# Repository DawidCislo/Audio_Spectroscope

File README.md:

# Audio_Spectroscope

This is an Audio Spectroscope made without using any kind of programmable devices. It uses over 120 ICs such as operational amplifiers, comparators and logic gates to create the effect you can see in the preview above.

# Theory of operation
The device consists of 11 PCBs, one backplane and 10 display modules. You can find the KiCad project files for the backplane in the 'ASP_Backplane' folder, and files for the display modules in the 'ASP_DIsplay' folder. On the backplane there are 2 3.5mm TRS sockets. Both of them are connected together, and the user can plug the source to one of the sockets, and headphones or speakers to the other, so there's no need to use a splitter. Next using a set of jumpers (JP1, JP2, JP3) the user can use either the left, right or both channels as the input for the spectroscope. Jumpers feed into a preamp with user-adjustable gain (U4A), so both quitet and loud listeners can see the spectroscope work. The series shottky diode (D4) protects the preamp from voltage spikes coming from the audio input and can be omitted.

The preamp feeds into 10 active band-pass filters that separate the audio signals into different bands. Those bands are: 32Hz, 63Hz, 125Hz, 250Hz, 500Hz, 1kHz, 2kHz, 4kHz, 8kHz and 16kHz. Each band is connected to a separate display module connector.

The backplane also has a power connector (5.5/2.1mm DC jack, center positive), for use with an external 12V 1A power supply, with a switch and some basic overvoltage protection. You can save on component cost by replacing the power switch (SW1) with a jumper, so that the device will always be on, and you can omit the TVS diode (D1) and replace both the fuse (F1) and reverse-circuit protection diode (D3) with a short - this will reduce resistance to voltage spikes coming from the external power supply.

Device uses an LM2576T for generating the 5V rail, the circuit has a voltage divider with resistor values calculated for an adjustable version of LM2576T, but if a fixed 5V version of this IC is available, simply omit R13 during assembly and replace R12 with a short.

Backplane also has a -10V source built using an MC34063 multi-purpose controller. Due to low current draw on the -10V rail, internal switching transistor is sufficient, simplifying the design.

Each display module has two peak detectors connected in series. The first detector made up of U3A, D1 and U3B has a smaller hold capacitor C12 and it's quickly discharged by R34. Output of this peak detector will show the current amplitude of a filtered audio signal. Next peak detector (U3C, D2 U3D) has a larger hold capacitor and it does not have a discharge resistor. Since it's connected to U3D and D2 it will still discharge, because of non-zero leakage currents of those components. Output of this slow peak detector will show the maximum amplitude of the audio signal and hold it there for a short while.

Both the fast and slow peak detector outputs are connected to 12 comparators each. Reference levels for the comparators are set by a long voltage divider in the middle. If a voltage on the input line is higher than the reference voltage set by the resistors, a comparator pulls the output low (since it has an open-collector output). In effect, the higher the voltage on the input line, the more comparators are switched off, and the more of their outputs have a logic low. On the fast side the comparators connect to logic NOT gates through some simple Resistor-Diode level shifter. On the slow side the comparators feed through voltage level shifters into Ex-OR gates. Each Ex-Or gate is connected to both it's own comparator, and the next comparator. If both of the comparator outputs are the same, the gate's output is low. Only in a situation, when the current level is different from the next one, the gate has a logic 1 on its output. As a result, for example, the fast side outputs '000001111111' while the slow side wil only output '000001000000'. 

The LEDs are driven by a pair of transistors each (Q2, Q3, Q4 ...). One transistor is controlled by the slow side, while the other one is controlled by the fast side. Transistors are connected in such a way, that either one can independently turn the LED on. Current of the LEDs is set by the series resistors (R8, R9, R10 ...), increasing the value of these resistors decreases the brightness of the LED, and reducing the value increases it. Different LEDs from different manufacturers might need adjustment of these resistor values to achieve a matching brightness for different colors. During the assembly of the first prototype I bought new red and green LEDs, but used old yellow LEDs that I had in stock. Since the old LEDs were much dimmer than the new ones, I used a lower value of resistance for yellow LEDs. Results may vary for your LEDs and it's much better to check them before soldering all 10 display modules.

#  Assembly tips and troubleshooting
>[!CAUTION]
>This device is ***VERY CHALLENGING TO ASSEMBLE*** There is a lot of small and hard to solder components (0603, TSSOP with 0.65mm pin pitch 4x0603 resistor networks, SOT-363s) packed very close together. On top of that there's over 1200 components to solder in total, and it will take very long time to assemble.
I recommend testing every PCB before connecting them together:
- Display modules: Connect all the supply rails on the angled connector to a corresponding voltage source, preferably use a multi-rail adjustable power supply. Next, connect the input of the display module to a potentiometer, generating a voltage between 0V and 5V. See if all the LEDs light up. Next rapidly turn the potentiometer down and see if all the LEDs light up as the slow peak detector discharges. If you see LEDs that are permamently off, check the series resistors and dual transistors next to the LEDs. If whole 4x or 6x sections refuse to light up or stay always on, check the ICs. If single LEDs stay on or light up in the wrong order, check the resistor networks. If the whole module refuses to light up, check the peak detector.
- Backplane: Check if there is no short on any power rails by sticking two pieces of wire into any of the display module connector and using a multimeter in a continuity mode. If there are no shorts on any of the rails, connect the external power supply, and then using the same 2 wires and a multimeter, now in voltage mode, check if all the supply rails have a correct voltage. Note: having a slightly lower voltage on both the 12V and -10V is still fine and will not prevent the device from wirking correctly.
Only after each PCB is thoroughly tested, you can connect them all together and see if the device really works. Display modules are packed very close together, so make sure that the LEDs don't short to the neighbouring modules. Now connect the audio cable and use an online tone generator ([like this one](https://www.szynalski.com/tone-generator/)) to test if the band-pass filters are working correctly.

If everything is working as it should, you can go ahead and assemble it together. I used a set of long M3 screws to tie all the display modules together and used a [TEKAL 31.29](https://www.tme.eu/pl/details/tekal31.29/obudowy-z-panelem/teko/tekal-31-29/) case. I've used thin strips of gray foil to stop light from bleeding between LEDs. In this preview you can see the first prototype, which had several major errors - they have been fixed and the files shared in this repository should be all good. On the animated preview and here, only 9 display modules are fitted - last module is broken and I can't figure out what exactly is wrong with it.
> [!NOTE]
> All those ICs packed so close together get pretty hot, and the hotter the circuit gets, the larger leakage currents are, and the faster the 'slow' peak detector falls. Drill a few ventillation holes or use a thermal pad to help dissipate the heat.

## Other information 
The project files were last edited in KiCad 7.0.9 and can be opened by any version that's newer than that.

Symbols and footprints used to create this project are part of my library, you can get it and use it for your projects here: [alternatekicadlibrary.com](https://alternatekicadlibrary.com/).

All the content within this repository is dedicated to the public domain under the [CC0 1.0 Universal (CC0 1.0) Public Domain Dedication](https://creativecommons.org/publicdomain/zero/1.0/).

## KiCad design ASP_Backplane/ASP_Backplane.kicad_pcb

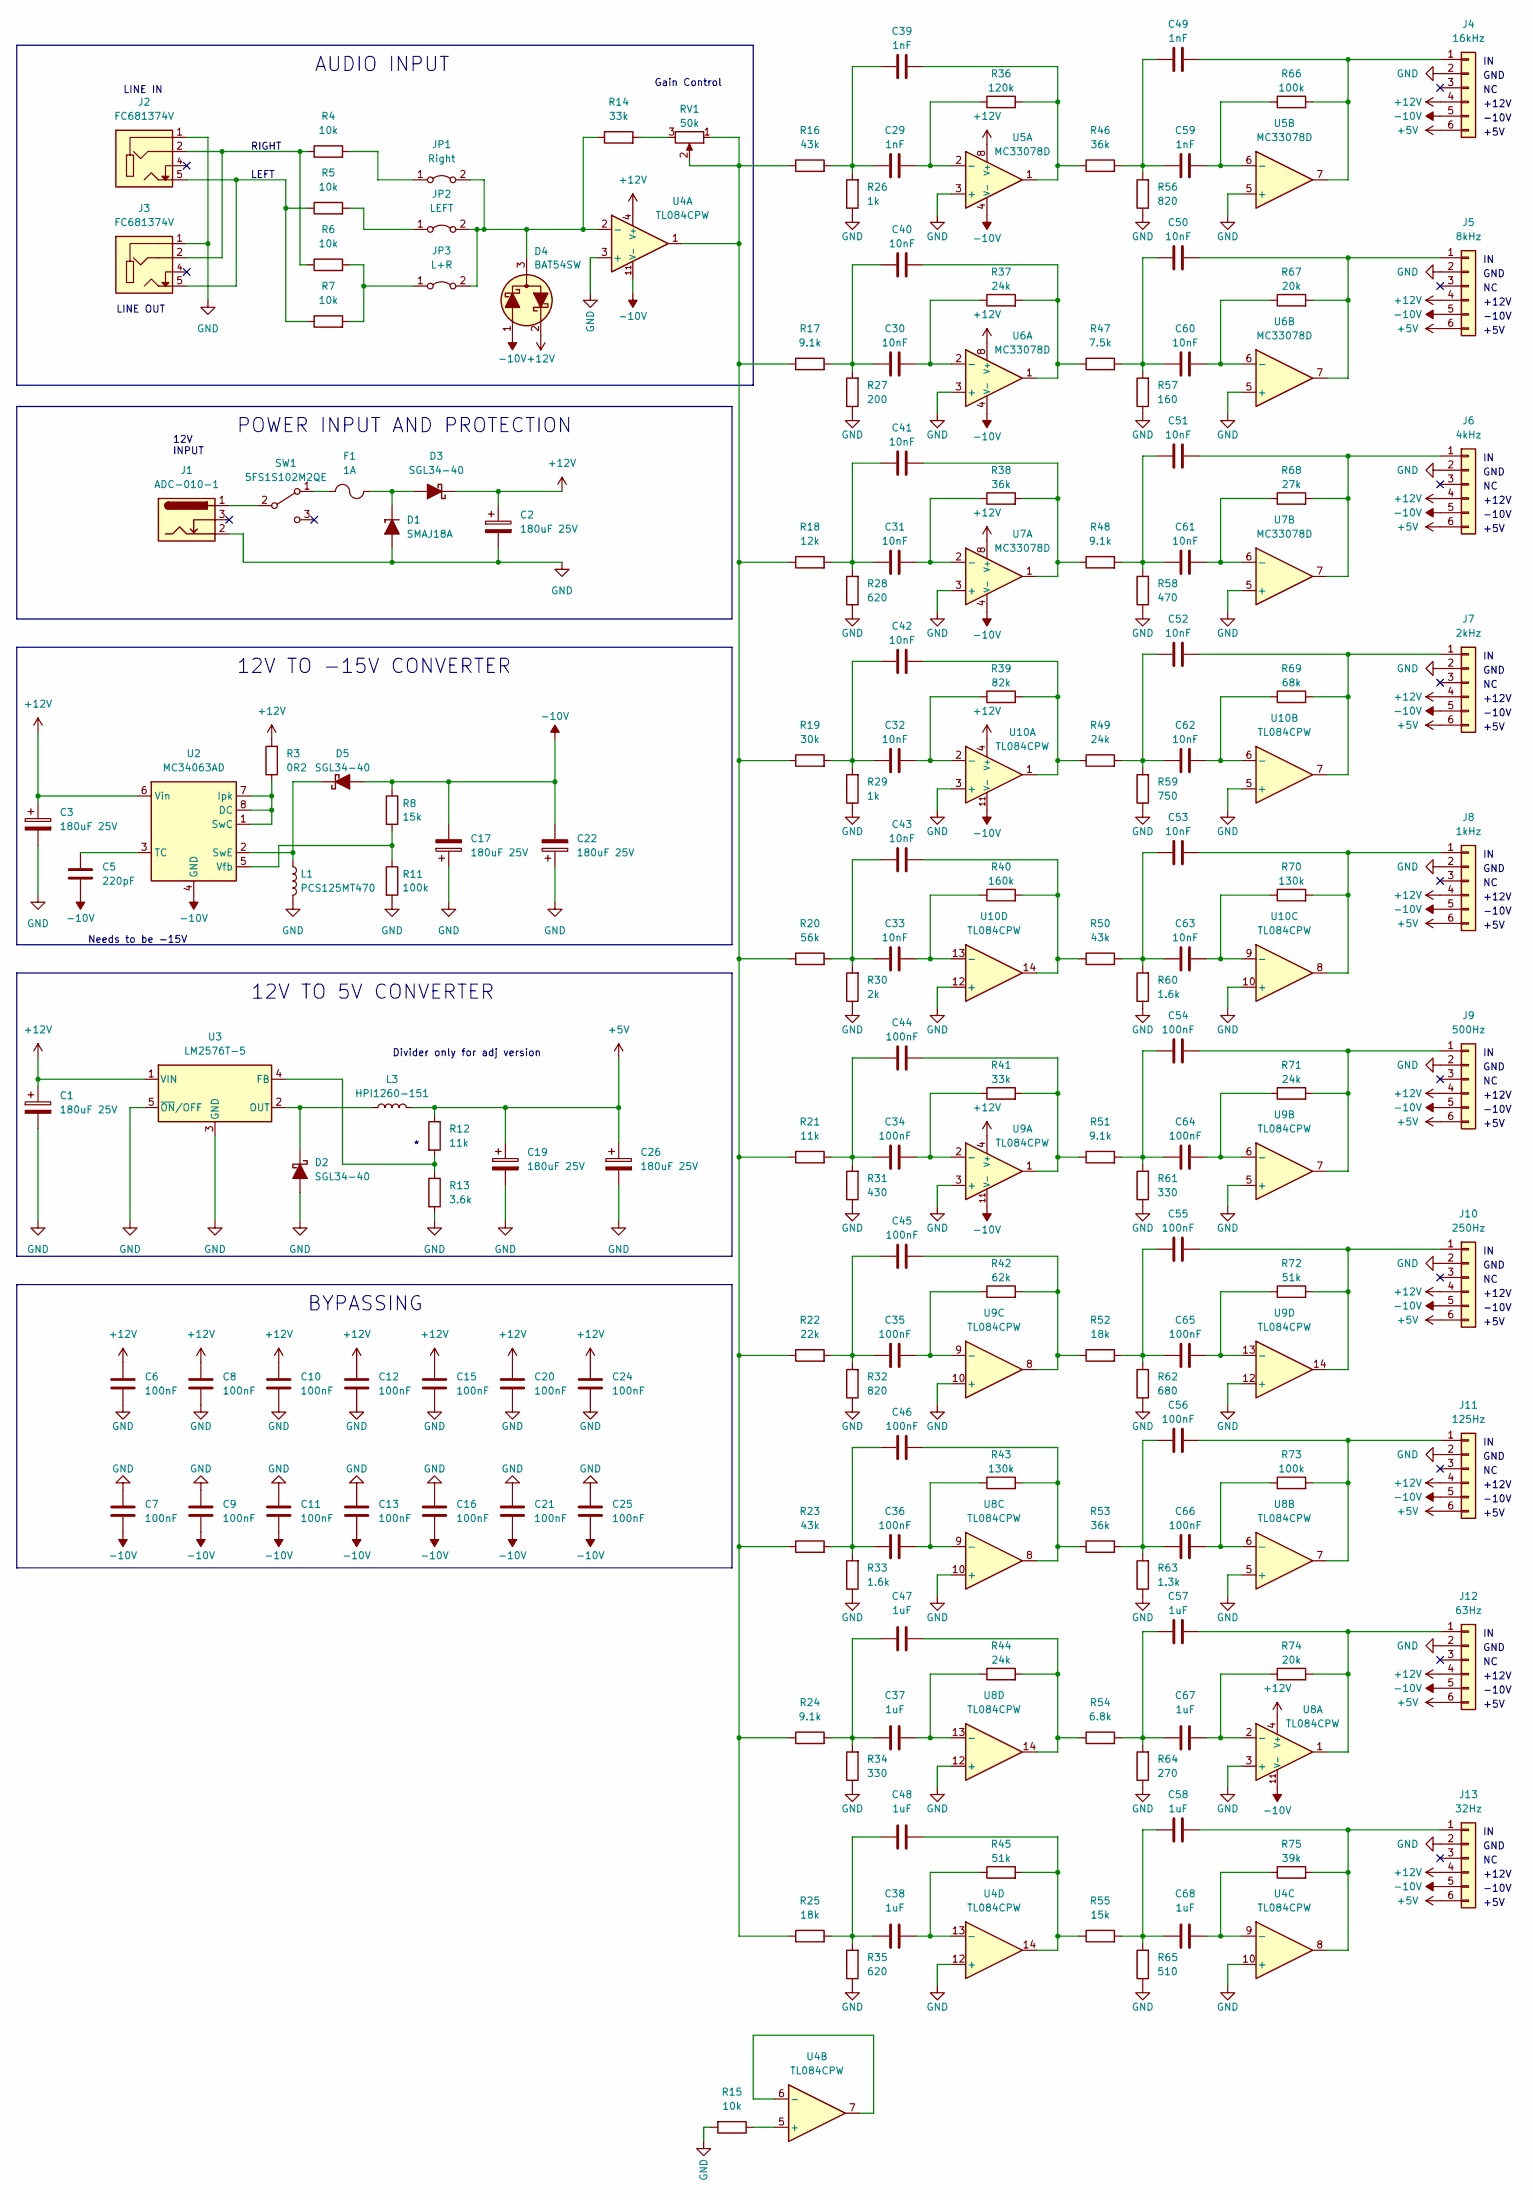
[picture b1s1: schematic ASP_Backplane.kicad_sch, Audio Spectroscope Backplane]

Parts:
C1, C2, C3, C17, C19, C22, C26: 180uF 25V; CP_Elec_6.3x7.7
C5: 220pF; C_0603_1608Metric
C6, C7, C8, C9, C10, C11, C12, C13, C15, C16, C20, C21, C24, C25, C34, C35, C36, C44, C45, C46, C54, C55, C56, C64, C65, C66: 100nF; C_0603_1608Metric
C29, C39, C49, C59: 1nF; C_0603_1608Metric
C30, C31, C32, C33, C40, C41, C42, C43, C50, C51, C52, C53, C60, C61, C62, C63: 10nF; C_0603_1608Metric
C37, C38, C47, C48, C57, C58, C67, C68: 1uF; C_0805_2012Metric
D1: SMAJ18A; D_SMA
D2, D3, D5: SGL34-40; D_MiniMELF
D4: BAT54SW; SOT-323_SC-70
F1: 1A; Fuse_1206_3216Metric
J1: ADC-010-1
J2, J3: FC681374V
J4: 16kHz; PinSocket_1x06_P2.54mm_Vertical
J5: 8kHz; PinSocket_1x06_P2.54mm_Vertical
J6: 4kHz; PinSocket_1x06_P2.54mm_Vertical
J7: 2kHz; PinSocket_1x06_P2.54mm_Vertical
J8: 1kHz; PinSocket_1x06_P2.54mm_Vertical
J9: 500Hz; PinSocket_1x06_P2.54mm_Vertical
J10: 250Hz; PinSocket_1x06_P2.54mm_Vertical
J11: 125Hz; PinSocket_1x06_P2.54mm_Vertical
J12: 63Hz; PinSocket_1x06_P2.54mm_Vertical
J13: 32Hz; PinSocket_1x06_P2.54mm_Vertical
JP1: Right; PinHeader_1x02_P2.54mm_Vertical
JP2: LEFT; PinHeader_1x02_P2.54mm_Vertical
JP3: L+R; PinHeader_1x02_P2.54mm_Vertical
L1: PCS125MT470; L_12x12mm_H6mm
L3: HPI1260-151; L_Wuerth_HCI-1365
R3: 0R2; R_2512_6332Metric
R4, R5, R6, R7, R15: 10k; R_0603_1608Metric
R8, R55: 15k; R_0603_1608Metric
R11, R66, R73: 100k; R_0603_1608Metric
R12, R21: 11k; R_0603_1608Metric
R13: 3.6k; R_0603_1608Metric
R14, R41: 33k; R_0603_1608Metric
R16, R23, R50: 43k; R_0603_1608Metric
R17, R24, R48, R51: 9.1k; R_0603_1608Metric
R18: 12k; R_0603_1608Metric
R19: 30k; R_0603_1608Metric
R20: 56k; R_0603_1608Metric
R22: 22k; R_0603_1608Metric
R25, R52: 18k; R_0603_1608Metric
R26, R29: 1k; R_0603_1608Metric
R27: 200; R_0603_1608Metric
R28, R35: 620; R_0603_1608Metric
R30: 2k; R_0603_1608Metric
R31: 430; R_0603_1608Metric
R32, R56: 820; R_0603_1608Metric
R33, R60: 1.6k; R_0603_1608Metric
R34, R61: 330; R_0603_1608Metric
R36: 120k; R_0603_1608Metric
R37, R44, R49, R71: 24k; R_0603_1608Metric
R38, R46, R53: 36k; R_0603_1608Metric
R39: 82k; R_0603_1608Metric
R40: 160k; R_0603_1608Metric
R42: 62k; R_0603_1608Metric
R43, R70: 130k; R_0603_1608Metric
R45, R72: 51k; R_0603_1608Metric
R47: 7.5k; R_0603_1608Metric
R54: 6.8k; R_0603_1608Metric
R57: 160; R_0603_1608Metric
R58: 470; R_0603_1608Metric
R59: 750; R_0603_1608Metric
R62: 680; R_0603_1608Metric
R63: 1.3k; R_0603_1608Metric
R64: 270; R_0603_1608Metric
R65: 510; R_0603_1608Metric
R67, R74: 20k; R_0603_1608Metric
R68: 27k; R_0603_1608Metric
R69: 68k; R_0603_1608Metric
R75: 39k; R_0603_1608Metric
RV1: 50k; Potentiometer_Alps_RK09K_Single_Vertical
SW1: 5FS1S102M2QE
U2: MC34063AD; SOIC-8_3.9x4.9mm_P1.27mm
U3: LM2576T-5; TO-220-5_P3.4x3.7mm_StaggerOdd_Lead3.8mm_Vertical
U4, U8, U9, U10: TL084CPW; TSSOP-14_4.4x5mm_P0.65mm
U5, U6, U7: MC33078D; SO-8_3.9x4.9mm_P1.27mm

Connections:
+5V: C19.1, C26.1, J4.6, J5.6, J6.6, J7.6, J8.6, J9.6, J10.6, J11.6, J12.6, J13.6, L3.2, R12.1
+12V: C1.1, C2.1, C3.1, C6.1, C8.1, C10.1, C12.1, C15.1, C20.1, C24.1, D3.1 (K), D4.2 (K), J4.4, J5.4, J6.4, J7.4, J8.4, J9.4, J10.4, J11.4, J12.4, J13.4, R3.2, U2.6 (Vin), U3.1 (VIN), U4.4 (V+), U5.8 (V+), U6.8 (V+), U7.8 (V+), U8.4 (V+), U9.4 (V+), U10.4 (V+)
-10V: C5.2, C7.2, C9.2, C11.2, C13.2, C16.2, C17.2, C21.2, C22.2, C25.2, D4.1 (A), D5.2 (A), J4.5, J5.5, J6.5, J7.5, J8.5, J9.5, J10.5, J11.5, J12.5, J13.5, R8.1, U2.4 (GND), U4.11 (V-), U5.4 (V-), U6.4 (V-), U7.4 (V-), U8.11 (V-), U9.11 (V-), U10.11 (V-)
GND: C1.2, C2.2, C3.2, C6.2, C7.1, C8.2, C9.1, C10.2, C11.1, C12.2, C13.1, C15.2, C16.1, C17.1, C19.2, C20.2, C21.1, C22.1, C24.2, C25.1, C26.2, D1.2 (A), D2.2 (A), J1.2, J2.1, J3.1, J4.2, J5.2, J6.2, J7.2, J8.2, J9.2, J10.2, J11.2, J12.2, J13.2, L1.2, R11.2, R13.2, R15.2, R26.1, R27.1, R28.1, R29.1, R30.1, R31.1, R32.1, R33.1, R34.1, R35.1, R56.1, R57.1, R58.1, R59.1, R60.1, R61.1, R62.1, R63.1, R64.1, R65.1, U3.3 (GND), U3.5 (~ON/OFF), U4.3 (+), U4.10 (+), U4.12 (+), U5.3 (+), U5.5 (+), U6.3 (+), U6.5 (+), U7.3 (+), U7.5 (+), U8.3 (+), U8.5 (+), U8.10 (+), U8.12 (+), U9.3 (+), U9.5 (+), U9.10 (+), U9.12 (+), U10.3 (+), U10.5 (+), U10.10 (+), U10.12 (+)
unnamed: C29.1, C39.1, R16.2, R26.2
unnamed: C30.1, C40.1, R17.2, R27.2
unnamed: C31.1, C41.1, R18.2, R28.2
unnamed: C32.1, C42.1, R19.2, R29.2
unnamed: C33.1, C43.1, R20.2, R30.2
unnamed: C34.1, C44.1, R21.2, R31.2
unnamed: C35.1, C45.1, R22.2, R32.2
unnamed: C36.1, C46.1, R23.2, R33.2
unnamed: C37.1, C47.1, R24.2, R34.2
unnamed: C38.1, C48.1, R25.2, R35.2
unnamed: C39.2, R36.2, R46.1, U5.1
unnamed: C40.2, R37.2, R47.1, U6.1
unnamed: C41.2, R38.2, R48.1, U7.1
unnamed: C42.2, R39.2, R49.1, U10.1
unnamed: C43.2, R40.2, R50.1, U10.14
unnamed: C44.2, R41.2, R51.1, U9.1
unnamed: C45.2, R42.2, R52.1, U9.8
unnamed: C46.2, R43.2, R53.1, U8.8
unnamed: C47.2, R44.2, R54.1, U8.14
unnamed: C48.2, R45.2, R55.1, U4.14
unnamed: C49.1, C59.1, R46.2, R56.2
unnamed: C50.1, C60.1, R47.2, R57.2
unnamed: C51.1, C61.1, R48.2, R58.2
unnamed: C52.1, C62.1, R49.2, R59.2
unnamed: C53.1, C63.1, R50.2, R60.2
unnamed: C54.1, C64.1, R51.2, R61.2
unnamed: C55.1, C65.1, R52.2, R62.2
unnamed: C56.1, C66.1, R53.2, R63.2
unnamed: C57.1, C67.1, R54.2, R64.2
unnamed: C58.1, C68.1, R55.2, R65.2
unnamed: D1.1 (K), D3.2 (A), F1.2
unnamed: D2.1 (K), L3.1, U3.2 (OUT)
unnamed: D4.3 (C), JP1.2 (B), JP2.2 (B), JP3.2 (B), R14.1, U4.2 (-)
unnamed: D5.1 (K), L1.1, U2.2 (SwE)
unnamed: J2.2, J3.2, R4.1, R6.1
unnamed: J2.5, J3.5, R5.1, R7.1
unnamed: C49.2, J4.1, R66.2, U5.7
unnamed: C50.2, J5.1, R67.2, U6.7
unnamed: C51.2, J6.1, R68.2, U7.7
unnamed: C52.2, J7.1, R69.2, U10.7
unnamed: C53.2, J8.1, R70.2, U10.8
unnamed: C54.2, J9.1, R71.2, U9.7
unnamed: C55.2, J10.1, R72.2, U9.14
unnamed: C56.2, J11.1, R73.2, U8.7
unnamed: C57.2, J12.1, R74.2, U8.1
unnamed: C58.2, J13.1, R75.2, U4.8
unnamed: JP1.1 (A), R4.2
unnamed: JP2.1 (A), R5.2
unnamed: JP3.1 (A), R6.2, R7.2
unnamed: R14.2, RV1.3
unnamed: R16.1, R17.1, R18.1, R19.1, R20.1, R21.1, R22.1, R23.1, R24.1, R25.1, RV1.1, RV1.2, U4.1
unnamed: F1.1, SW1.1 (A)
unnamed: J1.1, SW1.2 (B)
unnamed: R3.1, U2.1 (SwC), U2.7 (Ipk), U2.8 (DC)
unnamed: C5.1, U2.3 (TC)
unnamed: R8.2, R11.1, U2.5 (Vfb)
unnamed: R12.2, R13.1, U3.4 (FB)
unnamed: R15.1, U4.5 (+)
unnamed: U4.6 (-), U4.7
unnamed: C68.2, R75.1, U4.9 (-)
unnamed: C38.2, R45.1, U4.13 (-)
unnamed: C29.2, R36.1, U5.2 (-)
unnamed: C59.2, R66.1, U5.6 (-)
unnamed: C30.2, R37.1, U6.2 (-)
unnamed: C60.2, R67.1, U6.6 (-)
unnamed: C31.2, R38.1, U7.2 (-)
unnamed: C61.2, R68.1, U7.6 (-)
unnamed: C67.2, R74.1, U8.2 (-)
unnamed: C66.2, R73.1, U8.6 (-)
unnamed: C36.2, R43.1, U8.9 (-)
unnamed: C37.2, R44.1, U8.13 (-)
unnamed: C34.2, R41.1, U9.2 (-)
unnamed: C64.2, R71.1, U9.6 (-)
unnamed: C35.2, R42.1, U9.9 (-)
unnamed: C65.2, R72.1, U9.13 (-)
unnamed: C32.2, R39.1, U10.2 (-)
unnamed: C62.2, R69.1, U10.6 (-)
unnamed: C63.2, R70.1, U10.9 (-)
unnamed: C33.2, R40.1, U10.13 (-)

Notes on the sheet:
+5V
LINE OUT
GND
-10V
LINE IN
RIGHT
+12V
12V TO -15V CONVERTER
LEFT
AUDIO INPUT
Gain Control
BYPASSING
12V TO 5V CONVERTER
Needs to be -15V
Divider only for adj version
12V INPUT
POWER INPUT AND PROTECTION

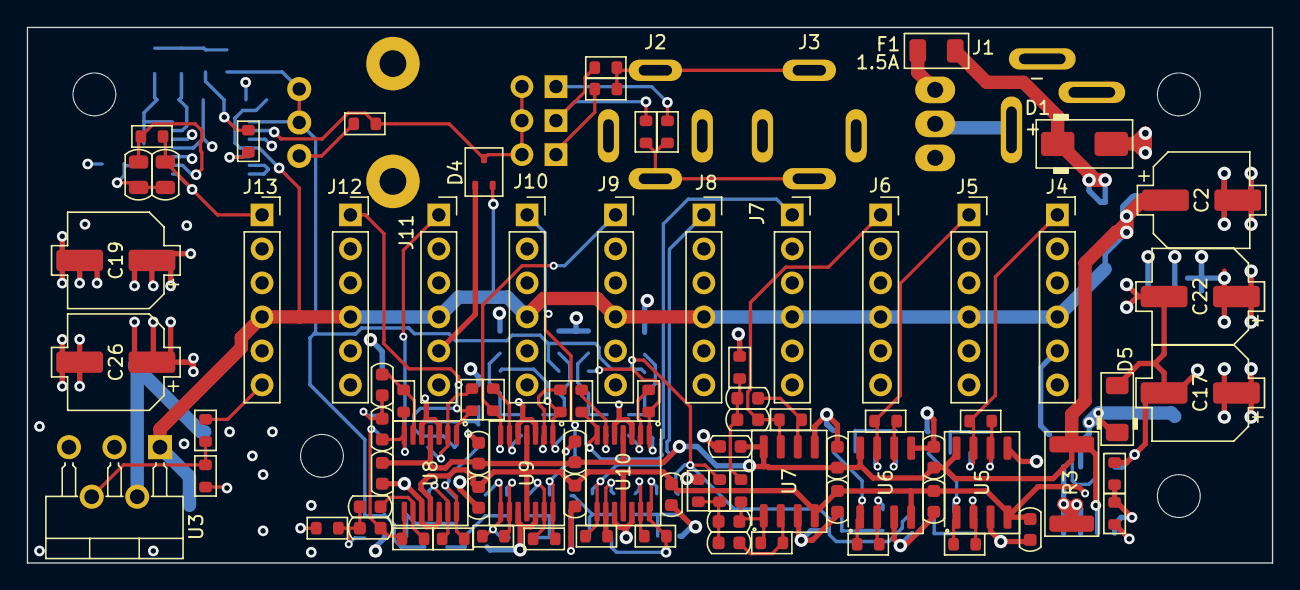
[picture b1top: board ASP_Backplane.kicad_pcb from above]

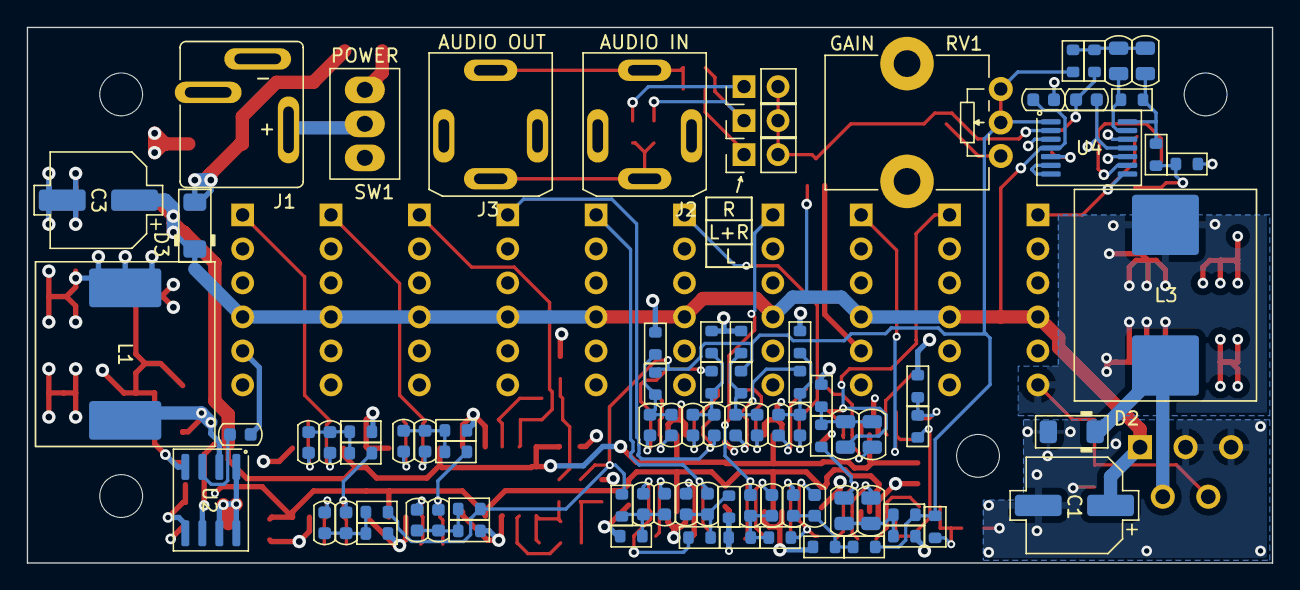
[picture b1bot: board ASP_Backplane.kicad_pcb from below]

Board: 4 copper layers, 93.0 x 40.0 mm, 168 parts (85 on the bottom side), 83 nets.

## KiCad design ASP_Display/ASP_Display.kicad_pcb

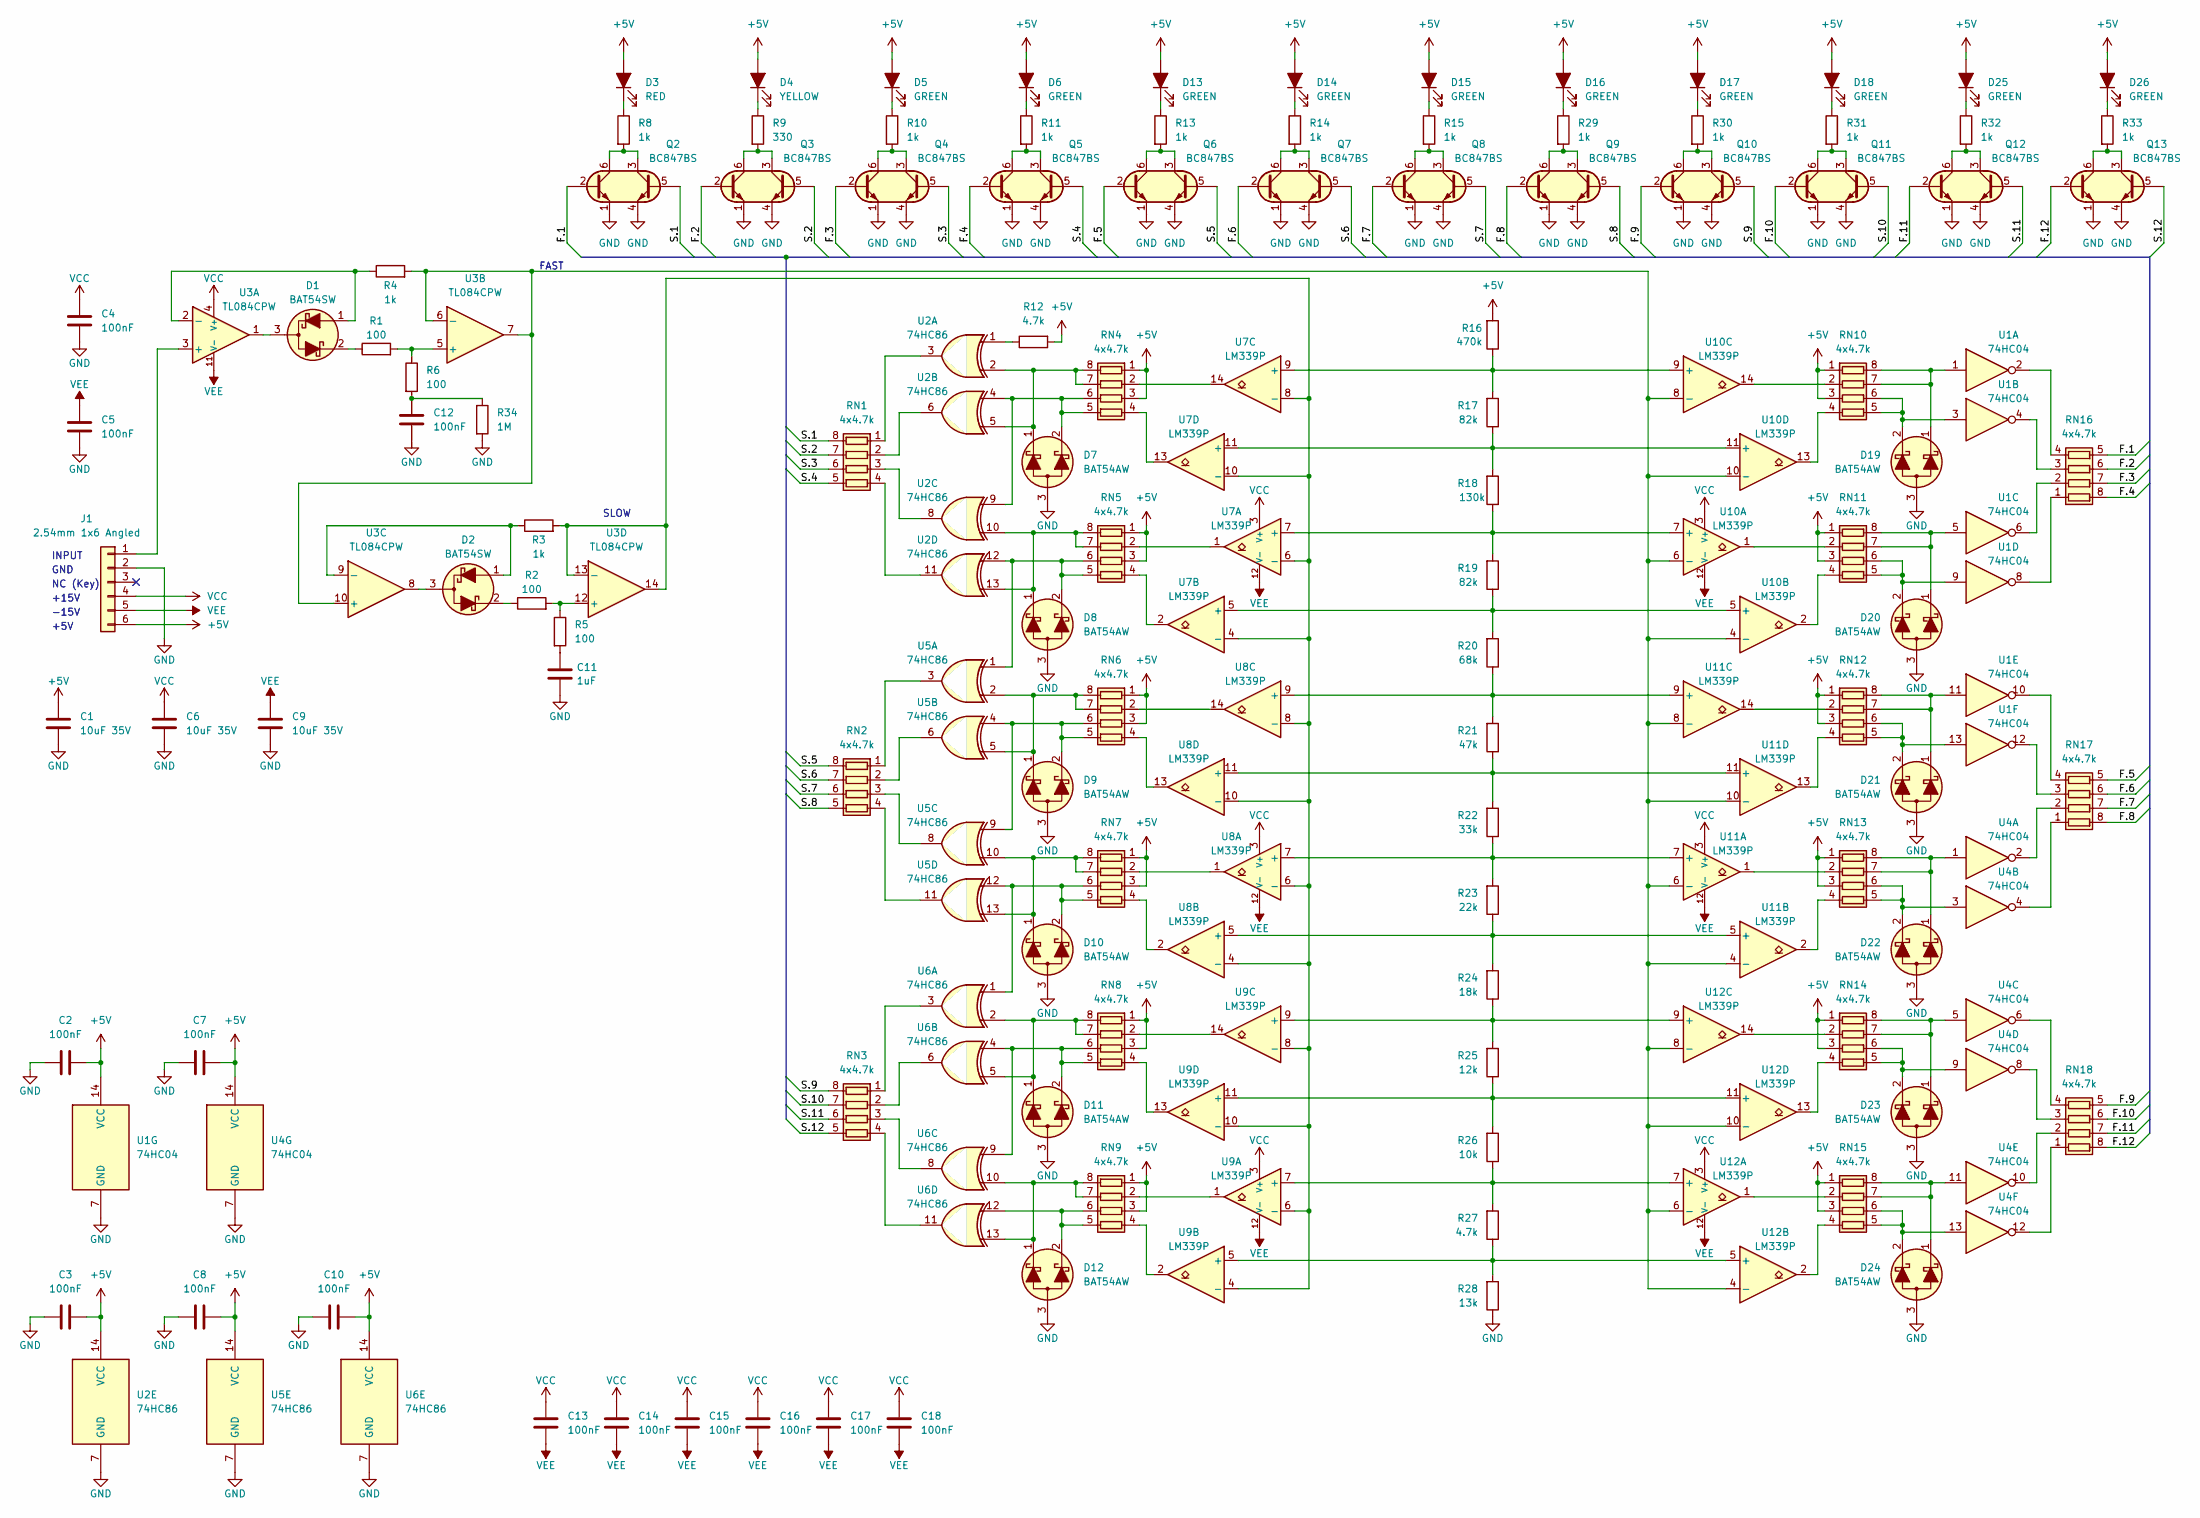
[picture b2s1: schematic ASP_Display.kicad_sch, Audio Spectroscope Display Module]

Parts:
C1, C6, C9: 10uF 35V; C_1206_3216Metric
C2, C3, C4, C5, C7, C8, C10, C12, C13, C14, C15, C16, C17, C18: 100nF; C_0603_1608Metric
C11: 1uF; C_0603_1608Metric
D1, D2: BAT54SW; SOT-323_SC-70
D3: RED; LED_Rectangular_W5.0mm_H2.0mm
D4: YELLOW; LED_Rectangular_W5.0mm_H2.0mm
D5, D6, D13, D14, D15, D16, D17, D18, D25, D26: GREEN; LED_Rectangular_W5.0mm_H2.0mm
D7, D8, D9, D10, D11, D12, D19, D20, D21, D22, D23, D24: BAT54AW; SOT-323_SC-70
J1: 2.54mm 1x6 Angled; PinHeader_1x06_P2.54mm_Horizontal
Q2, Q3, Q4, Q5, Q6, Q7, Q8, Q9, Q10, Q11, Q12, Q13: BC847BS; SOT-363_SC-70-6
R1, R2, R5, R6: 100; R_0603_1608Metric
R3, R4: 1k; R_0603_1608Metric
R8, R10, R11, R13, R14, R15, R29, R30, R31, R32, R33: 1k; R_0805_2012Metric
R9: 330; R_0805_2012Metric
R12, R27: 4.7k; R_0603_1608Metric
R16: 470k; R_0603_1608Metric
R17, R19: 82k; R_0603_1608Metric
R18: 130k; R_0603_1608Metric
R20: 68k; R_0603_1608Metric
R21: 47k; R_0603_1608Metric
R22: 33k; R_0603_1608Metric
R23: 22k; R_0603_1608Metric
R24: 18k; R_0603_1608Metric
R25: 12k; R_0603_1608Metric
R26: 10k; R_0603_1608Metric
R28: 13k; R_0603_1608Metric
R34: 1M; R_0603_1608Metric
RN1, RN2, RN3, RN4, RN5, RN6, RN7, RN8, RN9, RN10, RN11, RN12, RN13, RN14, RN15, RN16, RN17, RN18: 4x4.7k; R_Array_Convex_4x0603
U1, U4: 74HC04; TSSOP-14_4.4x5mm_P0.65mm
U2, U5, U6: 74HC86; TSSOP-14_4.4x5mm_P0.65mm
U3: TL084CPW; TSSOP-14_4.4x5mm_P0.65mm
U7, U8, U9, U10, U11, U12: LM339P; TSSOP-14_4.4x5mm_P0.65mm

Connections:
+5V: C1.1, C2.1, C3.1, C7.1, C8.1, C10.1, D3.2 (A), D4.2 (A), D5.2 (A), D6.2 (A), D13.2 (A), D14.2 (A), D15.2 (A), D16.2 (A), D17.2 (A), D18.2 (A), D25.2 (A), D26.2 (A), J1.6, R12.2, R16.2, RN4.1 (R1.1), RN4.3 (R3.1), RN5.1 (R1.1), RN5.3 (R3.1), RN6.1 (R1.1), RN6.3 (R3.1), RN7.1 (R1.1), RN7.3 (R3.1), RN8.1 (R1.1), RN8.3 (R3.1), RN9.1 (R1.1), RN9.3 (R3.1), RN10.1 (R1.1), RN10.3 (R3.1), RN11.1 (R1.1), RN11.3 (R3.1), RN12.1 (R1.1), RN12.3 (R3.1), RN13.1 (R1.1), RN13.3 (R3.1), RN14.1 (R1.1), RN14.3 (R3.1), RN15.1 (R1.1), RN15.3 (R3.1), U1.14 (VCC), U2.14 (VCC), U4.14 (VCC), U5.14 (VCC), U6.14 (VCC)
/F.1: Q2.2 (B1), RN16.5 (R4.2)
/F.2: Q3.2 (B1), RN16.6 (R3.2)
/F.3: Q4.2 (B1), RN16.7 (R2.2)
/F.4: Q5.2 (B1), RN16.8 (R1.2)
/F.5: Q6.2 (B1), RN17.5 (R4.2)
/F.6: Q7.2 (B1), RN17.6 (R3.2)
/F.7: Q8.2 (B1), RN17.7 (R2.2)
/F.8: Q9.2 (B1), RN17.8 (R1.2)
/F.9: Q10.2 (B1), RN18.5 (R4.2)
/F.10: Q11.2 (B1), RN18.6 (R3.2)
/F.11: Q12.2 (B1), RN18.7 (R2.2)
/F.12: Q13.2 (B1), RN18.8 (R1.2)
/S.1: Q2.5 (B2), RN1.8 (R1.2)
/S.2: Q3.5 (B2), RN1.7 (R2.2)
/S.3: Q4.5 (B2), RN1.6 (R3.2)
/S.4: Q5.5 (B2), RN1.5 (R4.2)
/S.5: Q6.5 (B2), RN2.8 (R1.2)
/S.6: Q7.5 (B2), RN2.7 (R2.2)
/S.7: Q8.5 (B2), RN2.6 (R3.2)
/S.8: Q9.5 (B2), RN2.5 (R4.2)
/S.9: Q10.5 (B2), RN3.8 (R1.2)
/S.10: Q11.5 (B2), RN3.7 (R2.2)
/S.11: Q12.5 (B2), RN3.6 (R3.2)
/S.12: Q13.5 (B2), RN3.5 (R4.2)
GND: C1.2, C2.2, C3.2, C4.1, C5.1, C6.2, C7.2, C8.2, C9.2, C10.2, C11.1, C12.1, D7.3 (A), D8.3 (A), D9.3 (A), D10.3 (A), D11.3 (A), D12.3 (A), D19.3 (A), D20.3 (A), D21.3 (A), D22.3 (A), D23.3 (A), D24.3 (A), J1.2, Q2.1 (E1), Q2.4 (E2), Q3.1 (E1), Q3.4 (E2), Q4.1 (E1), Q4.4 (E2), Q5.1 (E1), Q5.4 (E2), Q6.1 (E1), Q6.4 (E2), Q7.1 (E1), Q7.4 (E2), Q8.1 (E1), Q8.4 (E2), Q9.1 (E1), Q9.4 (E2), Q10.1 (E1), Q10.4 (E2), Q11.1 (E1), Q11.4 (E2), Q12.1 (E1), Q12.4 (E2), Q13.1 (E1), Q13.4 (E2), R28.1, R34.2, U1.7 (GND), U2.7 (GND), U4.7 (GND), U5.7 (GND), U6.7 (GND)
unnamed: C11.2, R5.2
unnamed: C12.2, R6.2, R34.1
unnamed: D1.1 (A), R4.1, U3.2 (-)
unnamed: D1.3 (C), U3.1
unnamed: D1.2 (K), R1.1
unnamed: D2.1 (A), R3.1, U3.9 (-)
unnamed: D2.3 (C), U3.8
unnamed: D2.2 (K), R2.1
unnamed: D3.1 (K), R8.1
unnamed: D4.1 (K), R9.1
unnamed: D5.1 (K), R10.1
unnamed: D6.1 (K), R11.1
unnamed: D7.1 (K1), RN4.7 (R2.2), RN4.8 (R1.2), U2.2, U2.5
unnamed: D7.2 (K2), RN4.5 (R4.2), RN4.6 (R3.2), U2.4, U2.9
unnamed: D8.1 (K1), RN5.7 (R2.2), RN5.8 (R1.2), U2.10, U2.13
unnamed: D8.2 (K2), RN5.5 (R4.2), RN5.6 (R3.2), U2.12, U5.1
unnamed: D9.1 (K1), RN6.7 (R2.2), RN6.8 (R1.2), U5.2, U5.5
unnamed: D9.2 (K2), RN6.5 (R4.2), RN6.6 (R3.2), U5.4, U5.9
unnamed: D10.1 (K1), RN7.7 (R2.2), RN7.8 (R1.2), U5.10, U5.13
unnamed: D10.2 (K2), RN7.5 (R4.2), RN7.6 (R3.2), U5.12, U6.1
unnamed: D11.1 (K1), RN8.7 (R2.2), RN8.8 (R1.2), U6.2, U6.5
unnamed: D11.2 (K2), RN8.5 (R4.2), RN8.6 (R3.2), U6.4, U6.9
unnamed: D12.1 (K1), RN9.7 (R2.2), RN9.8 (R1.2), U6.10, U6.13
unnamed: D12.2 (K2), RN9.5 (R4.2), RN9.6 (R3.2), U6.12
unnamed: D13.1 (K), R13.1
unnamed: D14.1 (K), R14.1
unnamed: D15.1 (K), R15.1
unnamed: D16.1 (K), R29.1
unnamed: D17.1 (K), R30.1
unnamed: D18.1 (K), R31.1
unnamed: D19.1 (K1), RN10.7 (R2.2), RN10.8 (R1.2), U1.1
unnamed: D19.2 (K2), RN10.5 (R4.2), RN10.6 (R3.2), U1.3
unnamed: D20.1 (K1), RN11.7 (R2.2), RN11.8 (R1.2), U1.5
unnamed: D20.2 (K2), RN11.5 (R4.2), RN11.6 (R3.2), U1.9
unnamed: D21.1 (K1), RN12.7 (R2.2), RN12.8 (R1.2), U1.11
unnamed: D21.2 (K2), RN12.5 (R4.2), RN12.6 (R3.2), U1.13
unnamed: D22.1 (K1), RN13.7 (R2.2), RN13.8 (R1.2), U4.1
unnamed: D22.2 (K2), RN13.5 (R4.2), RN13.6 (R3.2), U4.3
unnamed: D23.1 (K1), RN14.7 (R2.2), RN14.8 (R1.2), U4.5
unnamed: D23.2 (K2), RN14.5 (R4.2), RN14.6 (R3.2), U4.9
unnamed: D24.1 (K1), RN15.7 (R2.2), RN15.8 (R1.2), U4.11
unnamed: D24.2 (K2), RN15.5 (R4.2), RN15.6 (R3.2), U4.13
unnamed: D25.1 (K), R32.1
unnamed: D26.1 (K), R33.1
unnamed: J1.1, U3.3 (+)
unnamed: Q2.3 (C2), Q2.6 (C1), R8.2
unnamed: Q3.3 (C2), Q3.6 (C1), R9.2
unnamed: Q4.3 (C2), Q4.6 (C1), R10.2
unnamed: Q5.3 (C2), Q5.6 (C1), R11.2
unnamed: Q6.3 (C2), Q6.6 (C1), R13.2
unnamed: Q7.3 (C2), Q7.6 (C1), R14.2
unnamed: Q8.3 (C2), Q8.6 (C1), R15.2
unnamed: Q9.3 (C2), Q9.6 (C1), R29.2
unnamed: Q10.3 (C2), Q10.6 (C1), R30.2
unnamed: Q11.3 (C2), Q11.6 (C1), R31.2
unnamed: Q12.3 (C2), Q12.6 (C1), R32.2
unnamed: Q13.3 (C2), Q13.6 (C1), R33.2
unnamed: R12.1, U2.1
unnamed: RN1.1 (R1.1), U2.3
unnamed: RN1.2 (R2.1), U2.6
unnamed: RN1.3 (R3.1), U2.8
unnamed: RN1.4 (R4.1), U2.11
unnamed: RN2.1 (R1.1), U5.3
unnamed: RN2.2 (R2.1), U5.6
unnamed: RN2.3 (R3.1), U5.8
unnamed: RN2.4 (R4.1), U5.11
unnamed: RN3.1 (R1.1), U6.3
unnamed: RN3.2 (R2.1), U6.6
unnamed: RN3.3 (R3.1), U6.8
unnamed: RN3.4 (R4.1), U6.11
unnamed: RN4.2 (R2.1), U7.14
unnamed: RN4.4 (R4.1), U7.13
unnamed: RN5.2 (R2.1), U7.1
unnamed: RN5.4 (R4.1), U7.2
unnamed: RN6.2 (R2.1), U8.14
unnamed: RN6.4 (R4.1), U8.13
unnamed: RN7.2 (R2.1), U8.1
unnamed: RN7.4 (R4.1), U8.2
unnamed: RN8.2 (R2.1), U9.14
unnamed: RN8.4 (R4.1), U9.13
unnamed: RN9.2 (R2.1), U9.1
unnamed: RN9.4 (R4.1), U9.2
unnamed: RN10.2 (R2.1), U10.14
unnamed: RN10.4 (R4.1), U10.13
unnamed: RN11.2 (R2.1), U10.1
unnamed: RN11.4 (R4.1), U10.2
unnamed: RN12.2 (R2.1), U11.14
unnamed: RN12.4 (R4.1), U11.13
unnamed: RN13.2 (R2.1), U11.1
unnamed: RN13.4 (R4.1), U11.2
unnamed: RN14.2 (R2.1), U12.14
unnamed: RN14.4 (R4.1), U12.13
unnamed: RN15.2 (R2.1), U12.1
unnamed: RN15.4 (R4.1), U12.2
unnamed: RN16.1 (R1.1), U1.8
unnamed: RN16.2 (R2.1), U1.6
unnamed: RN16.3 (R3.1), U1.4
unnamed: RN16.4 (R4.1), U1.2
unnamed: RN17.1 (R1.1), U4.4
unnamed: RN17.2 (R2.1), U4.2
unnamed: RN17.3 (R3.1), U1.12
unnamed: RN17.4 (R4.1), U1.10
unnamed: RN18.1 (R1.1), U4.12
unnamed: RN18.2 (R2.1), U4.10
unnamed: RN18.3 (R3.1), U4.8
unnamed: RN18.4 (R4.1), U4.6
unnamed: R1.2, R6.1, U3.5 (+)
unnamed: R2.2, R5.1, U3.12 (+)
unnamed: R3.2, U3.13 (-), U3.14, U7.4 (-), U7.6 (-), U7.8 (-), U7.10 (-), U8.4 (-), U8.6 (-), U8.8 (-), U8.10 (-), U9.4 (-), U9.6 (-), U9.8 (-), U9.10 (-)
unnamed: R18.1, R19.2, U7.7 (+), U10.7 (+)
unnamed: R4.2, U3.6 (-), U3.7, U3.10 (+), U10.4 (-), U10.6 (-), U10.8 (-), U10.10 (-), U11.4 (-), U11.6 (-), U11.8 (-), U11.10 (-), U12.4 (-), U12.6 (-), U12.8 (-), U12.10 (-)
unnamed: R19.1, R20.2, U7.5 (+), U10.5 (+)
unnamed: R16.1, R17.2, U7.9 (+), U10.9 (+)
unnamed: R17.1, R18.2, U7.11 (+), U10.11 (+)
unnamed: R22.1, R23.2, U8.7 (+), U11.7 (+)
unnamed: R23.1, R24.2, U8.5 (+), U11.5 (+)
unnamed: R20.1, R21.2, U8.9 (+), U11.9 (+)
unnamed: R21.1, R22.2, U8.11 (+), U11.11 (+)
unnamed: R26.1, R27.2, U9.7 (+), U12.7 (+)
unnamed: R27.1, R28.2, U9.5 (+), U12.5 (+)
unnamed: R24.1, R25.2, U9.9 (+), U12.9 (+)
unnamed: R25.1, R26.2, U9.11 (+), U12.11 (+)
VCC: C4.2, C6.1, C13.2, C14.2, C15.2, C16.2, C17.2, C18.2, J1.4, U3.4 (V+), U7.3 (V+), U8.3 (V+), U9.3 (V+), U10.3 (V+), U11.3 (V+), U12.3 (V+)
VEE: C5.2, C9.1, C13.1, C14.1, C15.1, C16.1, C17.1, C18.1, J1.5, U3.11 (V-), U7.12 (V-), U8.12 (V-), U9.12 (V-), U10.12 (V-), U11.12 (V-), U12.12 (V-)

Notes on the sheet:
-15V
GND
NC (Key)
+15V
FAST
+5V
INPUT
SLOW

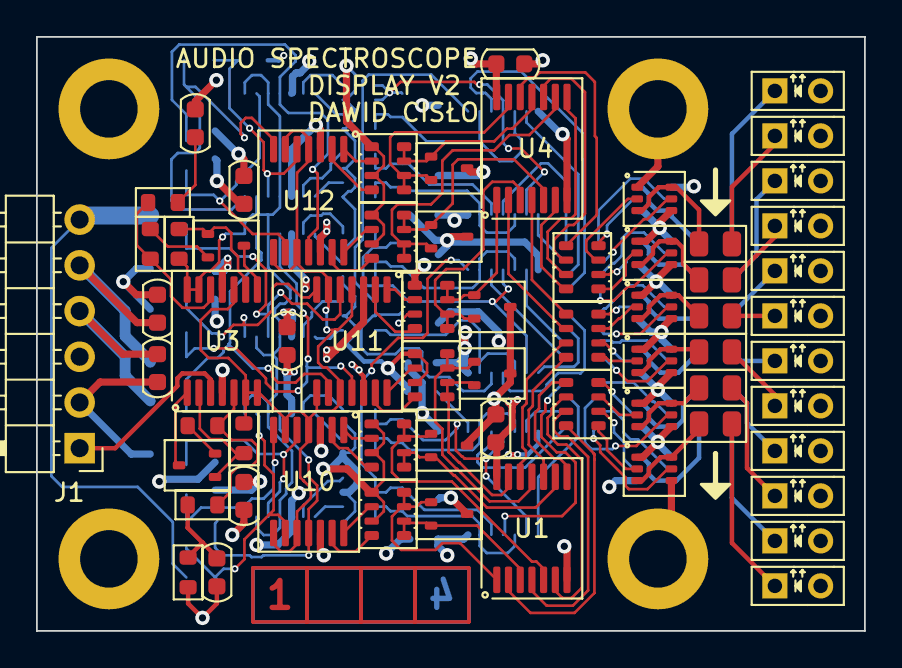
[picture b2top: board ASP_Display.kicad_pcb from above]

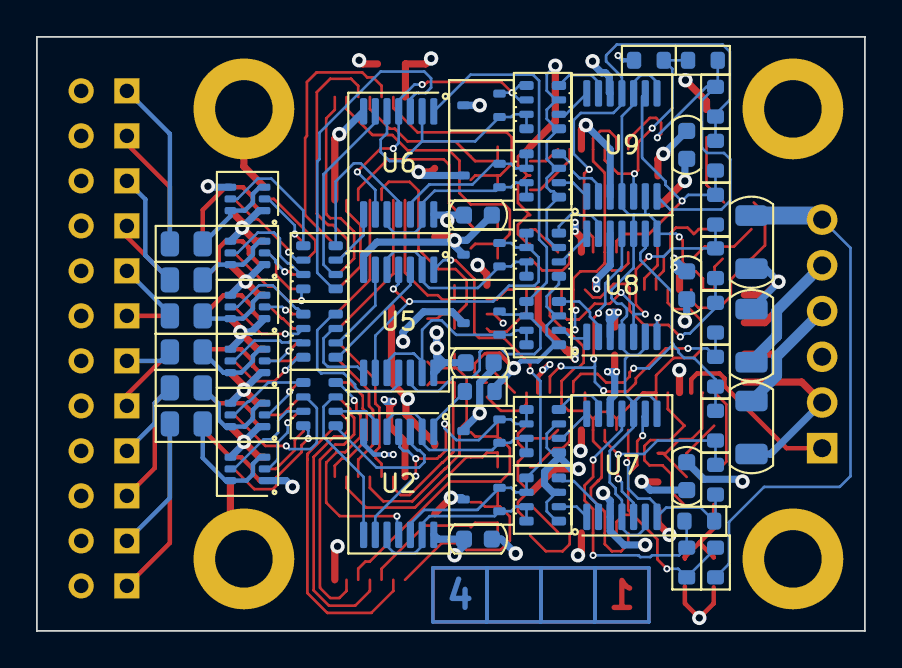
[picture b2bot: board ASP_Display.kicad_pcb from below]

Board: 4 copper layers, 46.0 x 33.0 mm, 120 parts (56 on the bottom side), 150 nets.

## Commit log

2024-02-19 Initial Commit
    Added main project files
2024-02-19 Update BOM and PDF documentation
2024-02-20 Create Gif_Preview
2024-02-20 Add documentation pictures
